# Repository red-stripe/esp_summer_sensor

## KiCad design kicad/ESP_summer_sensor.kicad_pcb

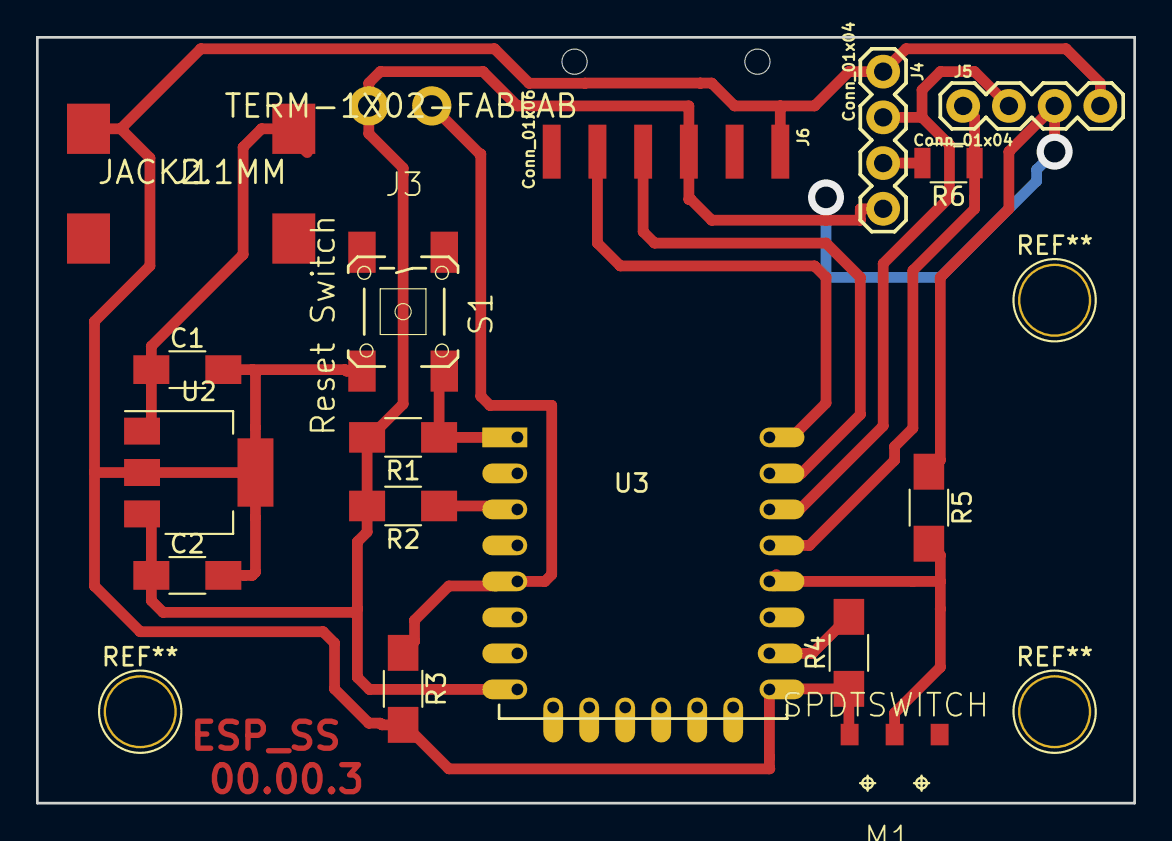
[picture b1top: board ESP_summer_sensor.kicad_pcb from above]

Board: 2 copper layers, 61.0 x 42.5 mm, 17 parts (0 on the bottom side), 12 nets.

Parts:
C1: 1uF; C_1206_HandSoldering
C2: 10uF; C_1206_HandSoldering
J1: JACK2.1MM; fab-JACK_2.1MM
J3: TERM-1X02-FABLAB; fab-ED555DS-2DS
J4, J5: Conn_01x04; 1X04
J6: Conn_01x06; 1X06-SMD_RA_MALE
M1: SPDTSWITCH; fab-AYZ0102AGRLC
R1, R2, R4, R5: 10K; R_1206_HandSoldering
R3: R; R_1206_HandSoldering
R6: 0; R_1206
S1: Reset Switch; fab-6MM_SWITCH
U2: MIC39100-3.3_SOT223; SOT-223-3_TabPin2
U3: ESP-12E

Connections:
+3V3: C2.1, J3.1, J4.4, J5.3, J6.3, R1.2, R2.2, R5.1, U2.3, U3.8
/Pulse: J3.2, R3.1, U3.5
/RXD: J6.4, U3.15
/RXI: J6.5, U3.16
/SCL: J4.2, J5.2, U3.14
/SDA: J4.3, J5.1, R6.1, R6.2, U3.13
GND: C1.2, C2.2, J1.CONT, J4.1, J5.4, J6.1, M1.1, R3.2, R4.1, S1.4, U2.2, U3.9
unnamed: M1.2, R5.2, U3.12
unnamed: R1.1, S1.2, U3.1
unnamed: R2.1, U3.3
unnamed: R4.2, U3.10
VIN: C1.1, J1.PIN, U2.1

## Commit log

2018-01-19 Add: gitignore
2018-01-19 Add: default platform files
2018-01-19 Add: code first pass
2018-01-22 Update: Nodemcu build config
2018-01-27 Update: oled basic display
2018-01-27 Update: Setting for HDC1080 sensor
2018-01-27 Update: add licence info for OTA
2018-01-27 Add: Wifi support
2018-01-27 Update: cycle info on oled screen
2018-01-27 Add: MQTT support to post data
2018-01-27 Update: ignore sensitive data
2018-01-27 Add: config.h example template
2018-01-27 Update: oled & mqtt tidy up Removed old comments, improved readability
2018-03-03 Update: MQTT & WIFI error output Print basic connection errors to oled screen
2018-03-03 Update: Ignore kicad temp files
2018-03-03 Add: Kicad sch Work in progress
2018-03-03 Update: power and pinouts on sch
2018-03-17 Update: Datasheet links & description
2018-04-10 Update: Kicad SCH & PCB Version 0.0.2
2018-04-11 Update: PCB version 00.00.3 Fixed layout and footprint issues
2018-04-11 Update: Mqtt debug info Moved message upload to its own function Pass error codes to display
2018-04-11 Add: mDNS support Basic setup for mDNS service lookup
2018-04-11 Update: minor code updates Rotates display text Upload settings for 00.00.3 PCB Define hostname on LAN
